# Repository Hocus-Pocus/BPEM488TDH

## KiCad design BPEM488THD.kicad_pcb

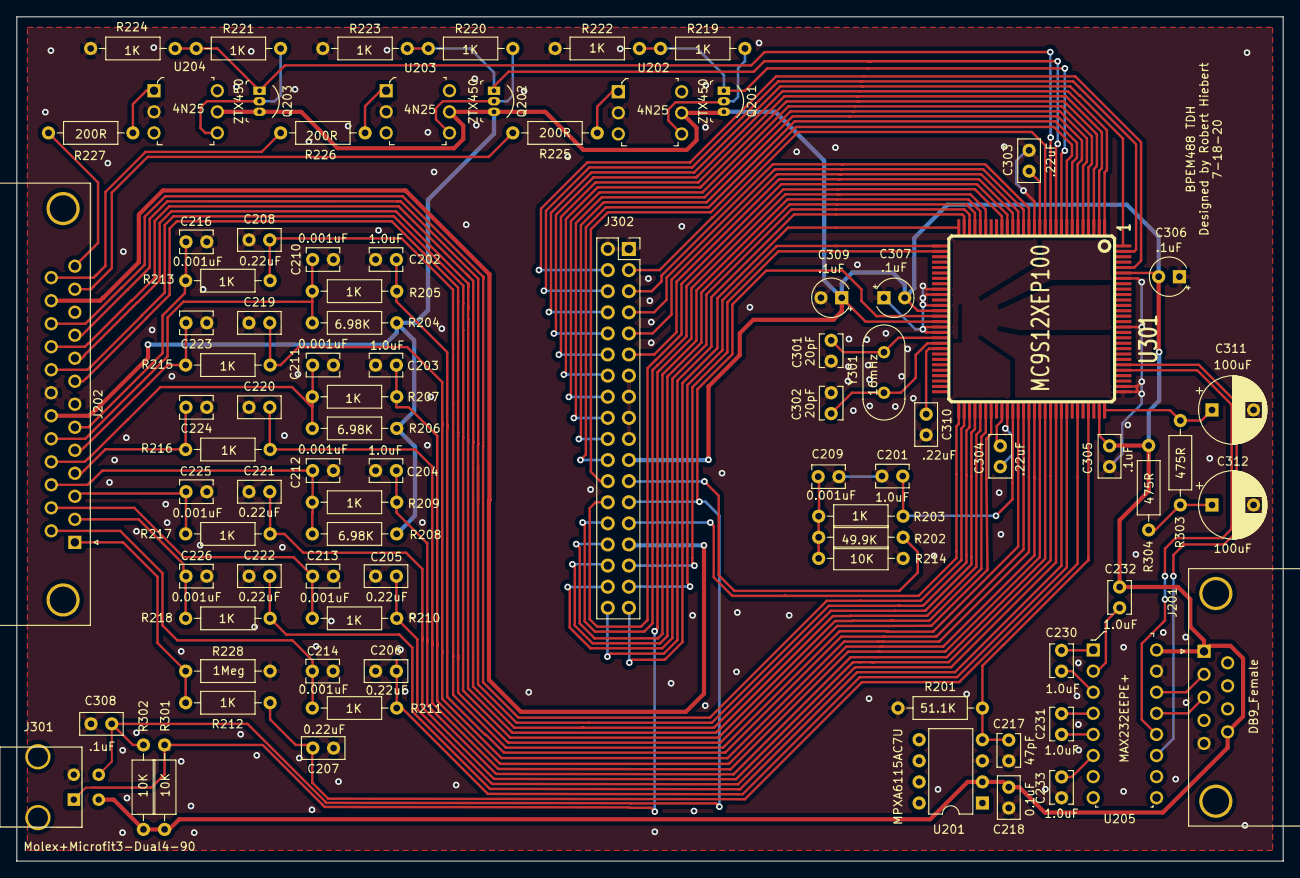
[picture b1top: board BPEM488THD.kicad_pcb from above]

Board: 2 copper layers, 152.4 x 101.6 mm, 87 parts (0 on the bottom side), 92 nets.

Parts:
C201, C202, C203, C204, C230, C231, C232, C233: 1.0uF; C_Disc_D3.8mm_W2.6mm_P2.50mm
C205, C206, C207, C208, C219, C220, C221, C222: 0.22uF; C_Disc_D5.0mm_W2.5mm_P2.50mm
C209, C210, C211, C212, C213, C214, C216, C223, C224, C225, C226: 0.001uF; C_Disc_D3.8mm_W2.6mm_P2.50mm
C217: 47pF; C_Disc_D3.8mm_W2.6mm_P2.50mm
C218: 0.1uF; C_Disc_D5.0mm_W2.5mm_P2.50mm
C301, C302: 20pF; C_Disc_D3.8mm_W2.6mm_P2.50mm
C303, C304, C310: .22uF; C_Disc_D5.0mm_W2.5mm_P2.50mm
C305, C308: .1uF; C_Disc_D5.0mm_W2.5mm_P2.50mm
C306, C307, C309: .1uF; CP_Radial_Tantal_D4.5mm_P2.50mm
C311, C312: 100uF; CP_Radial_D8.0mm_P5.00mm
J201: DB9_Female; DSUB-9_Female_Horizontal_P2.77x2.84mm_EdgePinOffset9.90mm_H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
J202: DB25_Female; DSUB-25_Female_Horizontal_P2.77x2.84mm_EdgePinOffset7.70mm_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
J301: Molex+Microfit3-Dual4-90; Molex-Microfit3-Dual4-90
J302: Conn_02x18_Odd_Even; PinSocket_2x18_P2.54mm_Vertical
Q201, Q202, Q203: ZTX450; TO-92-3
R201: 51.1K; R_Axial_DIN0207_L6.3mm_D2.5mm_P10.16mm_Horizontal
R202: 49.9K; R_Axial_DIN0207_L6.3mm_D2.5mm_P10.16mm_Horizontal
R203, R205, R207, R209, R210, R211, R212, R213, R215, R216, R217, R218, R219, R220, R221, R222, R223, R224: 1K; R_Axial_DIN0207_L6.3mm_D2.5mm_P10.16mm_Horizontal
R204, R206, R208: 6.98K; R_Axial_DIN0207_L6.3mm_D2.5mm_P10.16mm_Horizontal
R214, R301, R302: 10K; R_Axial_DIN0207_L6.3mm_D2.5mm_P10.16mm_Horizontal
R225, R226, R227: 200R; R_Axial_DIN0207_L6.3mm_D2.5mm_P10.16mm_Horizontal
R228: 1Meg; R_Axial_DIN0207_L6.3mm_D2.5mm_P10.16mm_Horizontal
R303, R304: 475R; R_Axial_DIN0207_L6.3mm_D2.5mm_P10.16mm_Horizontal
U201: MPXA6115AC7U; DIP-8_W7.62mm
U202, U203, U204: 4N25; DIP-6_W7.62mm
U205: MAX232EEPE+; DIP-16_W7.62mm
U301: MC9S12XEP100; PQFP112
Y301: 16mHz; Crystal_HC49-4H_Vertical

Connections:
+8V: J202.24, J302.29
+BATT: J302.23, R202.2
/CPU/PA0: J302.27, U301.57
/CPU/PB0: J302.30, U301.24
/CPU/PB1: J302.32, U301.25
/CPU/PB2: J302.34, U301.26
/CPU/PB3: J302.36, U301.27
/CPU/PB4: J302.35, U301.28
/CPU/PB5: J302.33, U301.29
/CPU/PB6: J302.31, U301.30
/CPU/PK0: J302.24, U301.8
/CPU/PK1: J302.22, U301.7
/CPU/PK2: J302.20, U301.6
/CPU/PK3: J302.18, U301.5
/CPU/PK4: J302.28, U301.20
/CPU/PK5: J302.26, U301.19
/CPU/PK7: J302.4, U301.108
/CPU/PP0: J302.16, U301.4
/CPU/PP1: J302.14, U301.3
/CPU/PP2: J302.12, U301.2
/CPU/PP3: J302.10, U301.1
/CPU/PP4: J302.8, U301.112
/CPU/PP5: J302.6, U301.111
/CPU/PT3: J302.3, U301.12
/CPU/PT4: J302.5, U301.15
/CPU/PT5: J302.7, U301.16
/CPU/PT6: J302.9, U301.17
/CPU/PT7: J302.11, U301.18
/CPU/RESET: C308.1, J301.4, J302.25, R302.2, U301.42
/Inputs_RS232/CKP: J202.25, R226.1
/Inputs_RS232/CLT: C210.2, J202.18, R204.1, R205.1
/Inputs_RS232/CMP: J202.12, R225.1
/Inputs_RS232/EFP: C223.2, J202.5, R215.1
/Inputs_RS232/EGO: J202.1, R212.1, R228.1
/Inputs_RS232/EOP: C216.2, J202.6, R213.1
/Inputs_RS232/Ftrm: C225.2, J202.3, R217.1
/Inputs_RS232/Itrm: C224.2, J202.4, R216.1
/Inputs_RS232/MAP: C213.2, J202.15, R210.1
/Inputs_RS232/MAT: C211.2, J202.17, R206.1, R207.1
/Inputs_RS232/PAD03in: C212.2, J202.16, R208.1, R209.1
/Inputs_RS232/PAD12in: C226.2, J202.2, R218.1
/Inputs_RS232/TPS: C214.2, J202.14, R211.1
/Inputs_RS232/VSPD: J202.13, R227.1
GND: C201.1, C202.1, C203.1, C204.1, C205.1, C206.1, C207.1, C208.1, C209.1, C210.1, C211.1, C212.1, C213.1, C214.1, C216.1, C217.1, C218.2, C219.1, C220.1, C221.1, C222.1, C223.1, C224.1, C225.1, C226.1, C233.1, C301.1, C302.1, C303.1, C304.1, C305.1, C306.1, C307.1, C308.2, C309.2, C310.2, C311.2, C312.2, J201.5, J202.7, J202.11, J202.20, J301.2, J302.1, J302.2, J302.13, J302.15, J302.17, J302.19, R201.2, R214.1, R222.1, R223.1, R224.1, R228.2, U201.3, U202.2, U203.2, U204.2, U205.15, U301.14, U301.37, U301.38, U301.40, U301.44, U301.45, U301.66, U301.85, U301.86, U301.97, U301.106
unnamed: C209.2, R202.1, R203.1, R214.2
unnamed: C230.1, U205.3
unnamed: C230.2, U205.1
unnamed: C231.1, U205.5
unnamed: C231.2, U205.4
unnamed: C232.1, U205.2
unnamed: C233.2, U205.6
unnamed: C301.2, U301.46, Y301.2
unnamed: C302.2, U301.47, Y301.1
unnamed: C303.2, U301.13
unnamed: C304.2, U301.65
unnamed: C310.1, U301.48
unnamed: C311.1, R303.1, U301.84
unnamed: C312.1, R303.2, R304.1
unnamed: J201.2, U205.14
unnamed: J201.3, U205.13
unnamed: J301.1, R301.2, U301.23
unnamed: Q201.2, R219.2, U202.4
unnamed: Q202.2, R220.2, U203.4
unnamed: Q203.2, R221.2, U204.4
unnamed: R225.2, U202.1
unnamed: R226.2, U203.1
unnamed: R227.2, U204.1
PA1: J202.23, U301.58
PA2: J202.10, U301.59
PA3: J202.22, U301.60
PA4: J202.9, U301.61
PA5: J202.21, U301.62
PA6: J202.8, U301.63
PAD00: C201.2, R203.2, U301.67
PAD01: C202.2, R205.2, U301.69
PAD02: C203.2, R207.2, U301.71
PAD03: C204.2, R209.2, U301.73
PAD04: C205.2, R210.2, U301.75
PAD05: C206.2, R211.2, U301.77
PAD06: C207.2, R212.2, U301.79
PAD07: C217.2, R201.1, U201.4, U301.81
PAD08: C208.2, R213.2, U301.68
PAD09: C219.2, R215.2, U301.70
PAD10: C220.2, R216.2, U301.72
PAD11: C221.2, R217.2, U301.74
PAD12: C222.2, R218.2, U301.76
PS0: U205.12, U301.89
PS1: U205.11, U301.90
PT0: Q201.1, R219.1, R222.2, U301.9
PT1: Q202.1, R220.1, R223.2, U301.10
PT2: Q203.1, R221.1, R224.2, U301.11
VDD: C218.1, C232.2, C305.2, C306.2, C307.2, C309.1, J201.1, J201.9, J202.19, J301.3, J302.21, Q201.3, Q202.3, Q203.3, R204.2, R206.2, R208.2, R301.1, R302.1, R304.2, U201.2, U202.5, U203.5, U204.5, U205.16, U301.41, U301.43, U301.83, U301.107
